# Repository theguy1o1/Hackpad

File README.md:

hi guys this is my first ever hardware project and was a lot of fun i learnt a lot and i hope to keep doing so.

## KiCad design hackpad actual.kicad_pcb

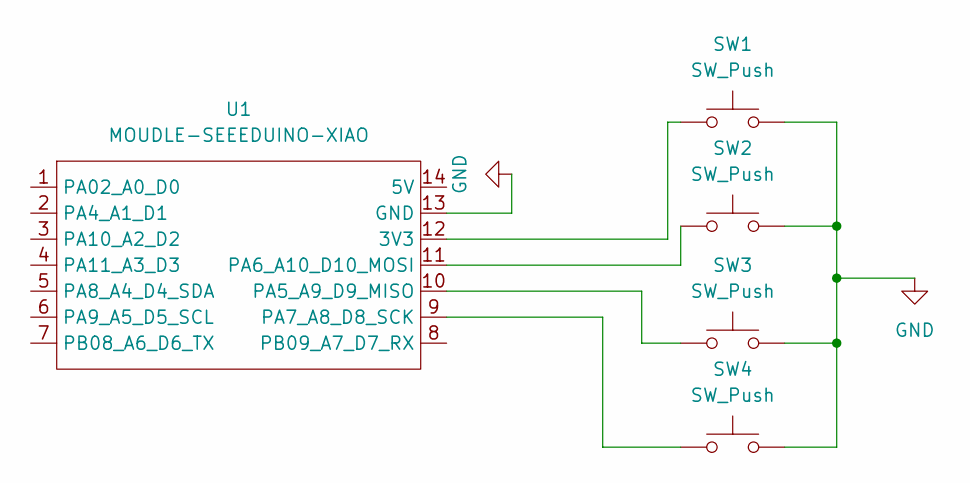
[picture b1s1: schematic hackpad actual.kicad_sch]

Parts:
SW1, SW2, SW3, SW4: SW_Push; SW_Cherry_MX_1.00u_PCB
U1: MOUDLE-SEEEDUINO-XIAO; XIAO-Generic-Hybrid-14P-2.54-21X17.8MM

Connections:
GND: SW1.2, SW2.2, SW3.2, SW4.2, U1.13 (GND)
unnamed: SW1.1, U1.12 (3V3)
unnamed: SW3.1, U1.10 (PA5_A9_D9_MISO)
unnamed: SW2.1, U1.11 (PA6_A10_D10_MOSI)
unnamed: SW4.1, U1.9 (PA7_A8_D8_SCK)

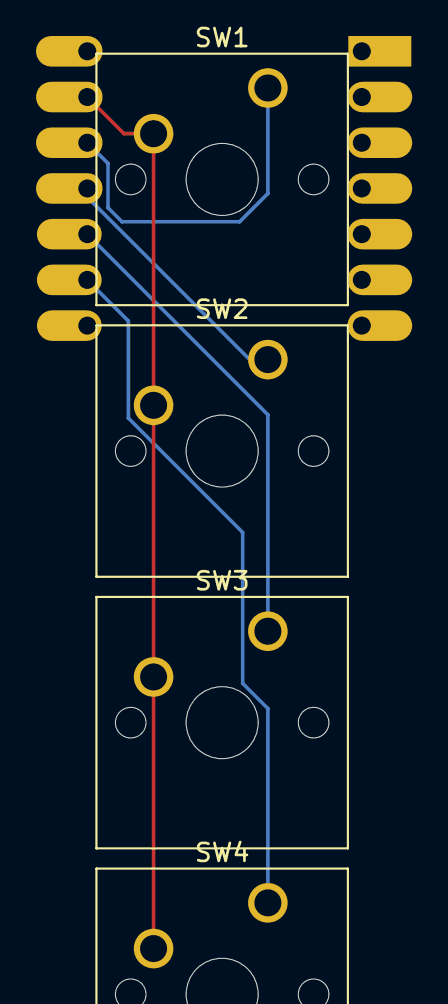
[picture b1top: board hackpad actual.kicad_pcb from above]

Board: 2 copper layers, 5 parts (1 on the bottom side), 5 nets.

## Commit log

2026-02-26 Create info
2026-02-26 Update and rename hackpad actual.kicad_pcb to hardware/hakpadpcb
2026-02-26 Rename hackpad actual.kicad_prl to hardware/hackpad actual.kicad_prl
2026-02-26 Rename hackpad actual.kicad_pro to hardware/hackpad actual.kicad_pro
2026-02-26 Create BOM
